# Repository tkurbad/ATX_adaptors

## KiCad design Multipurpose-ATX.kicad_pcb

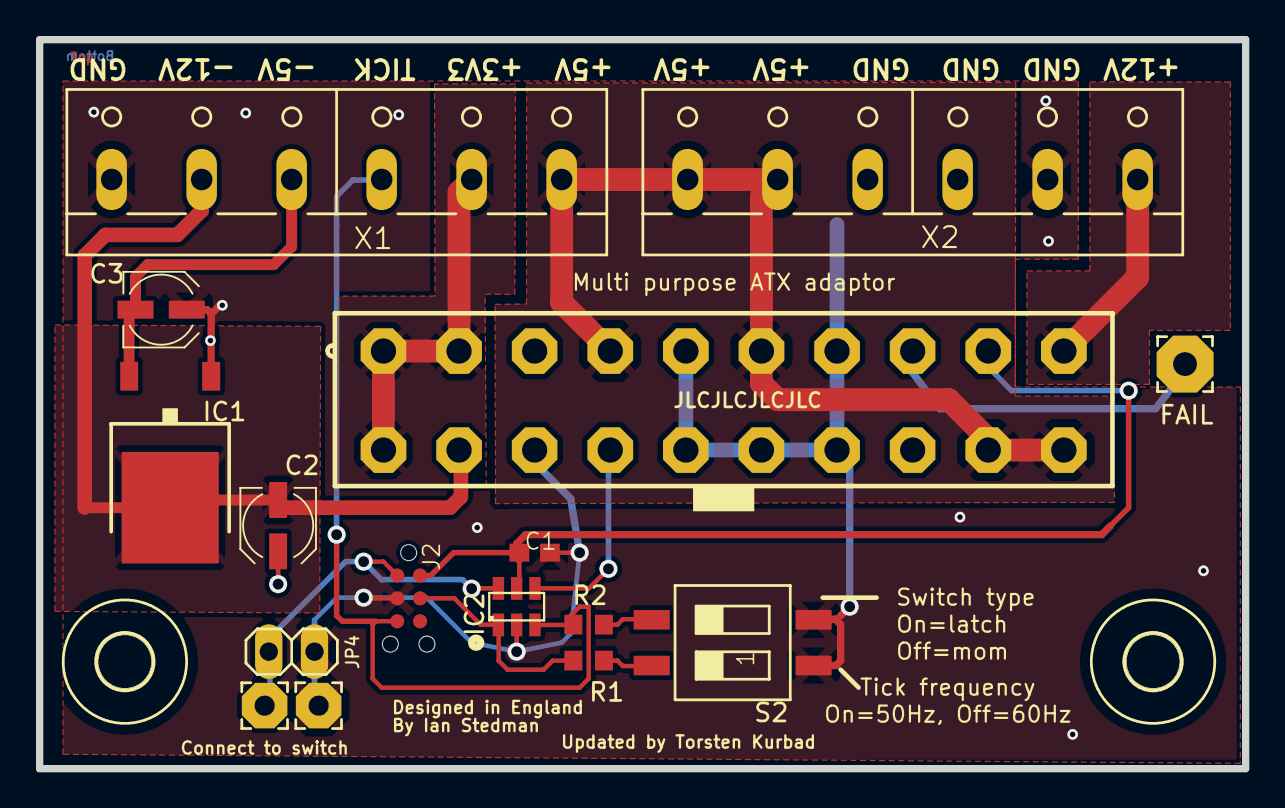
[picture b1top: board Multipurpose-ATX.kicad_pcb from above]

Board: 2 copper layers, 67.0 x 40.5 mm, 18 parts (0 on the bottom side), 14 nets.

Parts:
C1: 100nF; C0603
C2: 1uF; UD-4X5,8_NICHICON
C3: 2.2uF; UD-4X5,8_NICHICON
FAIL: 3,17_1,3
H1, H2: MOUNT-HOLE3.0; 3,0
IC1: MC79M05CDTG; DPACK_3
IC2: PIC10F202; SOT23-6
J1: ATXP20; MOLEX39281203
J2: TC2030-MCP-NL
JP4: 1X02
PAD1, PAD2: 2,54_1,1
R1, R2: 2K2; R0603
S2: SWS002; SMS-002
X1, X2: W237-6

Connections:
+3V3: J1.1, J1.2, J1.11, X1.5
+5VPOWER: J1.4, J1.6, J1.19, J1.20, X1.6, X2.1, X2.2
+5VSB: C1.1, IC2.5, J1.9, J2.2
+12VPOWER: J1.10, X2.6
-12VPOWER: C2.-, IC1.4, J1.12, X1.2
FAIL: FAIL.1, J1.8
GND: C1.2, C2.+, C3.+, IC1.1, IC2.2, J1.3, J1.5, J1.7, J1.13, J1.15, J1.16, J1.17, J2.3, JP4.1, PAD2.1, S2.1, S2.2, X1.1, X2.3, X2.4, X2.5
unnamed: R2.2, S2.3
unnamed: R1.2, S2.4
unnamed: C3.-, IC1.3, X1.3
PCLK: IC2.3, J2.5, R2.1, X1.4
PDAT: IC2.1, J2.4, R1.1
PWRON: IC2.4, J1.14
SWITCH1: IC2.6, J2.1, JP4.2, PAD1.1

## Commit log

2023-09-19 Imported to KiCAD / Adapted to put out an additional 3.3V / Minor modifications / Interactive BOM

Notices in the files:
parts and their libraries:
©2009 ROFA.cz - modified and updated by Robert Darlington ‹rdarlington@gmail.com›
